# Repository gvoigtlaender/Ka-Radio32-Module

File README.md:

# Ka-Radio32-Module
Ka-Radio32 module to mount on top of VS1053 module

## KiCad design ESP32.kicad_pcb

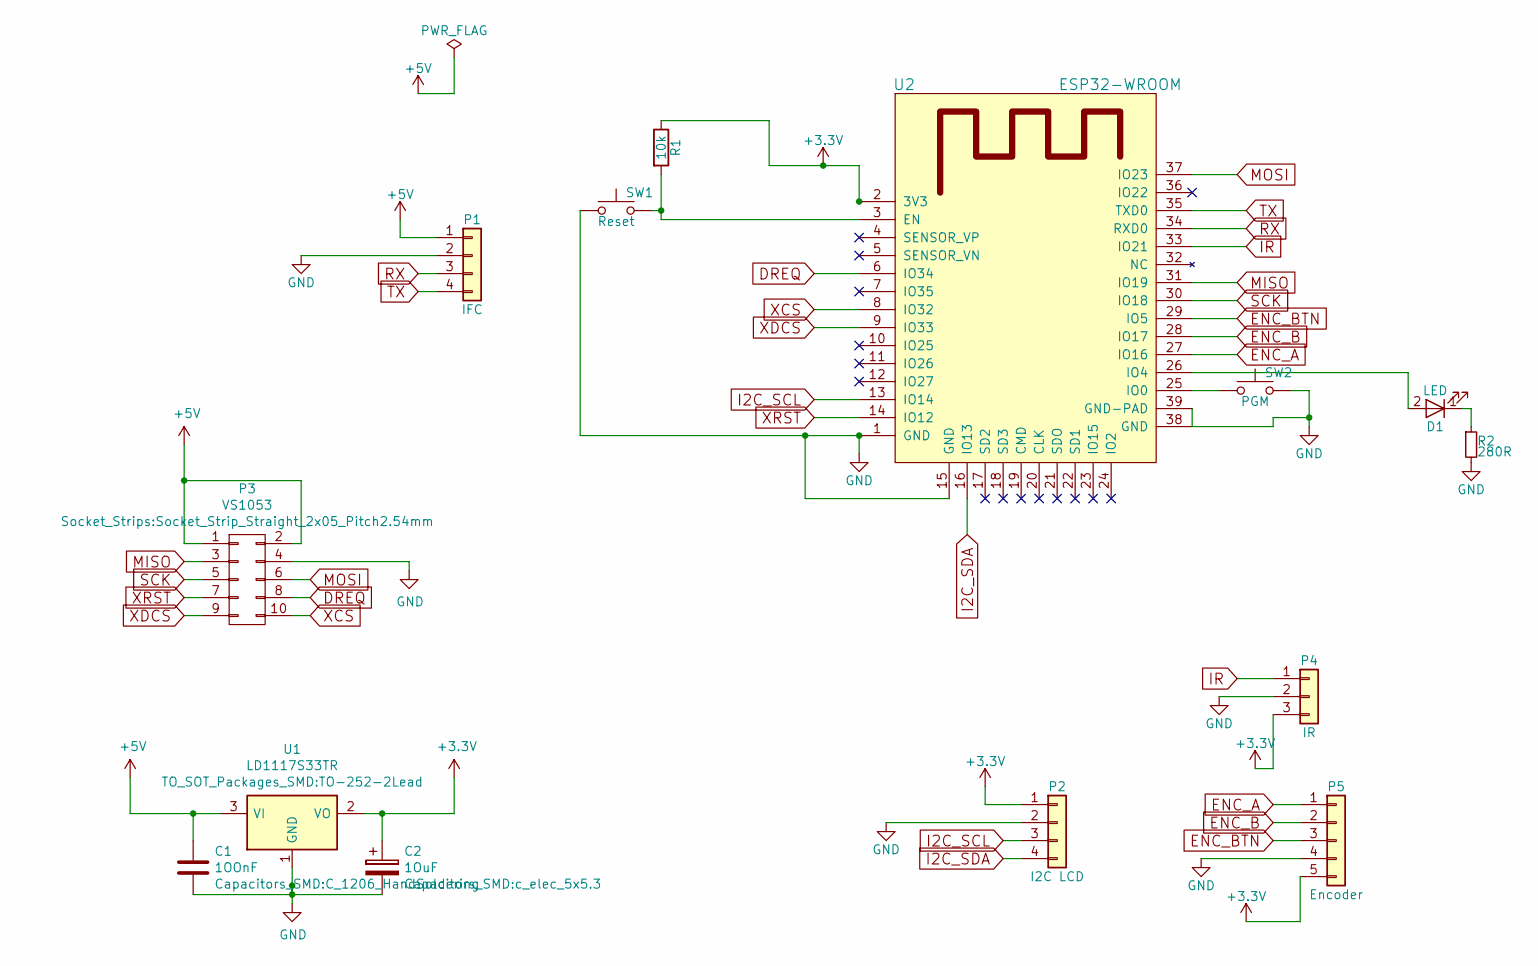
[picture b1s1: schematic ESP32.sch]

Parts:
C1: 1OOnF; C_1206_HandSoldering
C2: 1OuF; c_elec_5x5.3
D1: LED; LED_D3.0mm
P1: IFC; Pin_Header_Straight_1x04_Pitch2.54mm
P2: I2C LCD; Pin_Header_Straight_1x04_Pitch2.54mm
P3: VS1053; Socket_Strip_Straight_2x05_Pitch2.54mm
P4: IR; Pin_Header_Straight_1x03_Pitch2.54mm
P5: Encoder; Pin_Header_Straight_1x05_Pitch2.54mm
R1: 10k; R_0805_HandSoldering
R2: 280R; R_0805_HandSoldering
SW1: Reset; SW_PUSH_6mm_h5mm
SW2: PGM; SW_PUSH_6mm_h5mm
U1: LD1117S33TR; TO-252-2Lead
U2: ESP32-WROOM

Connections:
+3V3: C2.1, P2.1, P4.3, P5.5, R1.1, U1.2 (VO), U2.2 (3V3)
+5V: C1.1, P1.1, P3.1, P3.2, U1.3 (VI); also elsewhere on the board
DREQ: P3.8, U2.6 (IO34)
ENC_A: P5.1, U2.27 (IO16)
ENC_B: P5.2, U2.28 (IO17)
ENC_BTN: P5.3, U2.29 (IO5)
GND: C1.2, C2.2, P1.2, P2.2, P3.4, P4.2, P5.4, R2.2, SW1.1, SW2.2, U1.1 (GND), U2.1 (GND), U2.15 (GND), U2.38 (GND), U2.39 (GND-PAD); also elsewhere on the board
I2C_SCL: P2.3, U2.13 (IO14)
I2C_SDA: P2.4, U2.16 (IO13)
IR: P4.1, U2.33 (IO21)
MISO: P3.3, U2.31 (IO19)
MOSI: P3.6, U2.37 (IO23)
unnamed: D1.1 (K), R2.1
unnamed: D1.2 (A), U2.26 (IO4)
unnamed: R1.2, SW1.2, U2.3 (EN)
unnamed: SW2.1, U2.25 (IO0)
RX: P1.3, U2.34 (RXD0)
SCK: P3.5, U2.30 (IO18)
TX: P1.4, U2.35 (TXD0)
XCS: P3.10, U2.8 (IO32)
XDCS: P3.9, U2.9 (IO33)
XRST: P3.7, U2.14 (IO12)

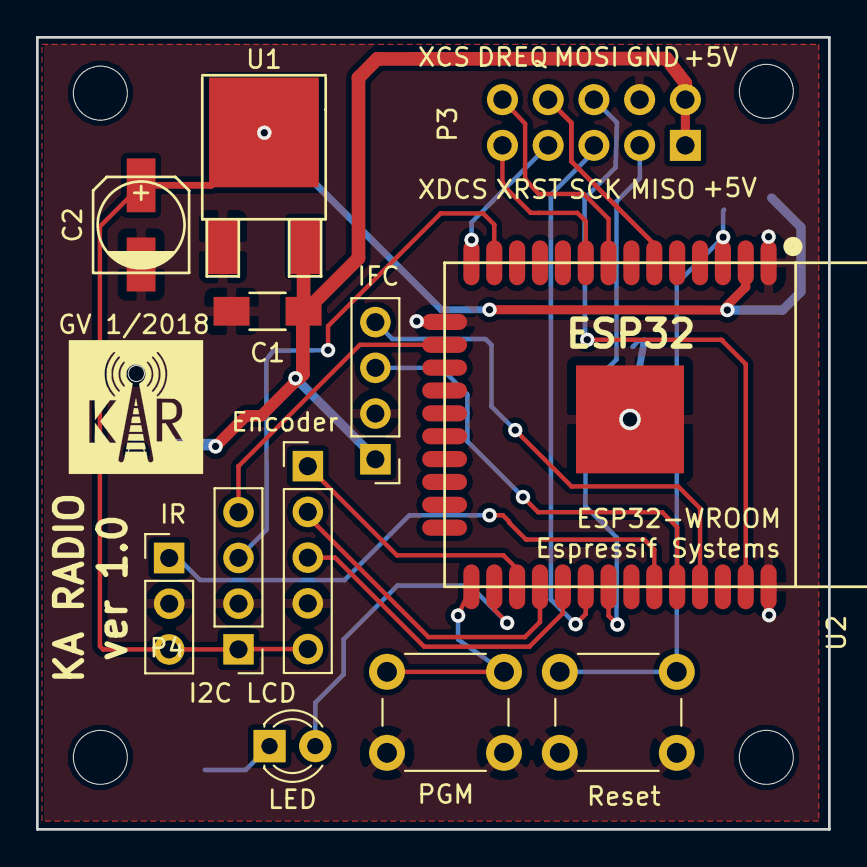
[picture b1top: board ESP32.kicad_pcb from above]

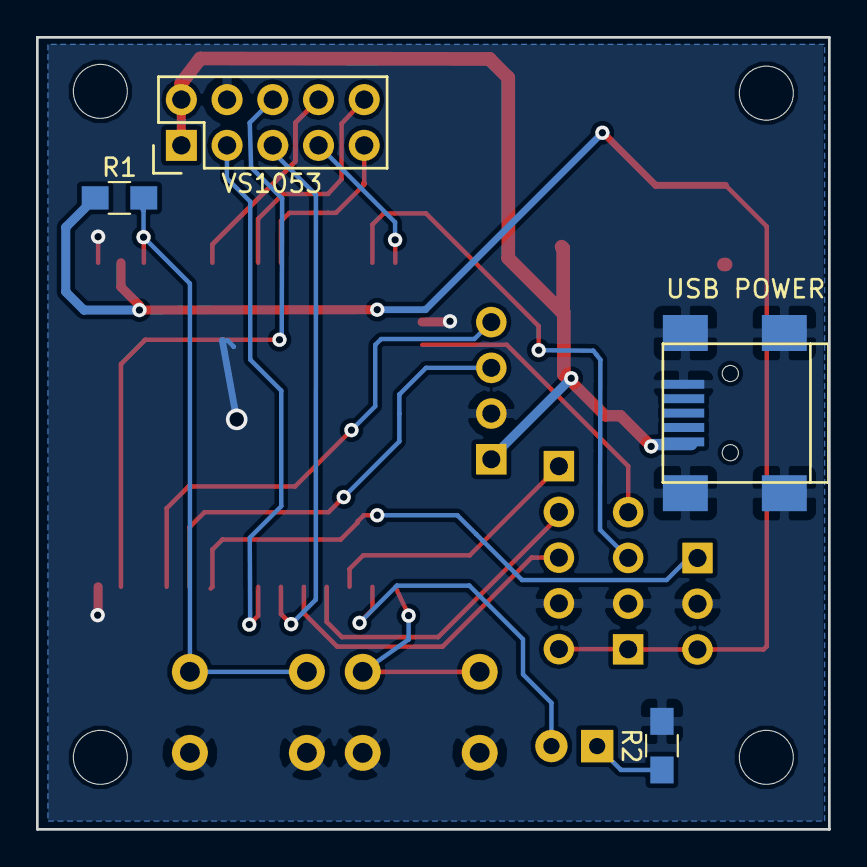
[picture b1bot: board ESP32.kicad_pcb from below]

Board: 2 copper layers, 44.0 x 44.0 mm, 19 parts (4 on the bottom side), 22 nets.

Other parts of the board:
REF01, REF2, REF3, REF4: MountingHole_3mm
USB POWER: USB_Mini-B

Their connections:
+5V: USB POWER.1; also elsewhere on the board
GND: USB POWER.5, USB POWER.6; also elsewhere on the board

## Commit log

2018-02-17 Create d
